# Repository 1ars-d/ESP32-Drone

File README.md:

# ESP32 Custom Drone

## 🚁 Overview

A compact, custom-built **5.5″ quadcopter drone** powered by an **ESP32 microcontroller**. This project includes both hardware design (3D-printed components, PCB layout) and firmware (Arduino-based) for flight control.

---

## 🔧 Firmware

The flight control software is written in **C++** using the **Arduino framework**. It runs a **250Hz control loop** to maintain drone stability using the following key features:

- **Sensor Fusion**: A **Kalman Filter** fuses gyroscope and accelerometer data to estimate orientation.
- **Control System**: Stabilization is achieved using a **cascaded PID control loop**.
- **Remote Input**: Directional control is handled via a **radio receiver**.
- **Live PID Tuning**: The drone can host a **local Wi-Fi web interface** for real-time PID tuning.
  > _The web-based tuning interface was adapted from [pratikPhadte/ESP32-Flight-controller-](https://github.com/pratikPhadte/ESP32-Flight-controller-)._

---

## 🛠️ Hardware Components

| Component             | Description                                                | Price   |
| --------------------- | ---------------------------------------------------------- | ------- |
| **Frame**             | FlyFishRC FIFTY5                                           | €50.00  |
| **Radio Receiver**    | Flysky FS-IA6B                                             | €20.00  |
| **Flight Controller** | ESP32-DevKitC, MP1584 (Buck Converter), MPU6050 (IMU), PCB | €20.00  |
| **Motors**            | 4x FlyfishRC Flash 2306 1750Kv                             | €60.00  |
| **ESC**               | 30.5mm 4-in-1 40A BLHeli32                                 | €50.00  |
| **Battery**           | 3S 1500mAh LiPo                                            | €20.00  |
| **Propellers**        | 4x 5.5″ Props                                              | €2.50   |
| **3D Printed Parts**  | Material cost for FC Case, RC Case, Feet                   | €2.00   |
| **Total**             |                                                            | €224,50 |

> Note: The listed prices are approximate and may vary depending on the retailer or manufacturer. In this build, we intentionally used some higher-quality (and more expensive) components to ensure that budget parts wouldn't become a limiting factor in performance. However, with careful sourcing and smart purchasing decisions, the overall cost of this drone can be significantly reduced.

---

## 🧠 Flight Controller

The flight controller (FC) is based on an **ESP32 DevKitC**, mounted on a custom PCB. It integrates:

- **MPU6050 IMU** for motion sensing
- **MP1584 buck converter** to step down 10V (from ESC) to 5V

Connections are made via **JST SH cables** to the ESC and radio receiver.

> ‼️ The VCC wire of the JST SH connector for the radio receiver is connected to the ESP32’s 3.3V output. However, the receiver used in this project (FS-IA6B) requires a minimum operating voltage of 4.0V. To address this, an additional VCC wire was manually soldered to the ESP32’s 5V pin to provide sufficient power. While some 5V receivers may appear to function at 3.3V in test setups, our testing showed that the receiver's output becomes unstable when the motors are running, likely due to temporary voltage drops. For reliable performance, ensure the receiver is properly powered with a stable 5V supply.

---

## 🧾 PCB Design

Designed using **KiCad** and manufactured by **JLCPCB**.

### 🔌 Schematic

### 🔄 Routing

### 3D Model

---

## 🖨️ 3D Printed Parts

All parts were designed in **Autodesk Fusion 360** and printed using **PLA**. **M2/M3 threaded heat inserts** are used to mount components to the carbon frame.

### 📦 Flight Controller Case

### 📡 Radio Receiver Case

### 🧩 Miscellaneous Parts

**Spacers**  

**Feet**  
Model from [Cults3D – FlyFishRC Volador Arm Protection](https://cults3d.com/de/modell-3d/spiel/flyfishrc-volador-5-6-full-arm-protection)  

---

## 👥 Contributors

- Tilman Kurmayer (https://github.com/tchello45)
- Melina Leitermann (https://github.com/me1ina1)

## 📚 References & Inspirations

This project was inspired and guided by the following open-source resources:

- [CarbonAeronautics/Manual-Quadcopter-Drone](https://github.com/CarbonAeronautics/Manual-Quadcopter-Drone)
- [pratikPhadte/ESP32-Flight-controller-](https://github.com/pratikPhadte/ESP32-Flight-controller-)

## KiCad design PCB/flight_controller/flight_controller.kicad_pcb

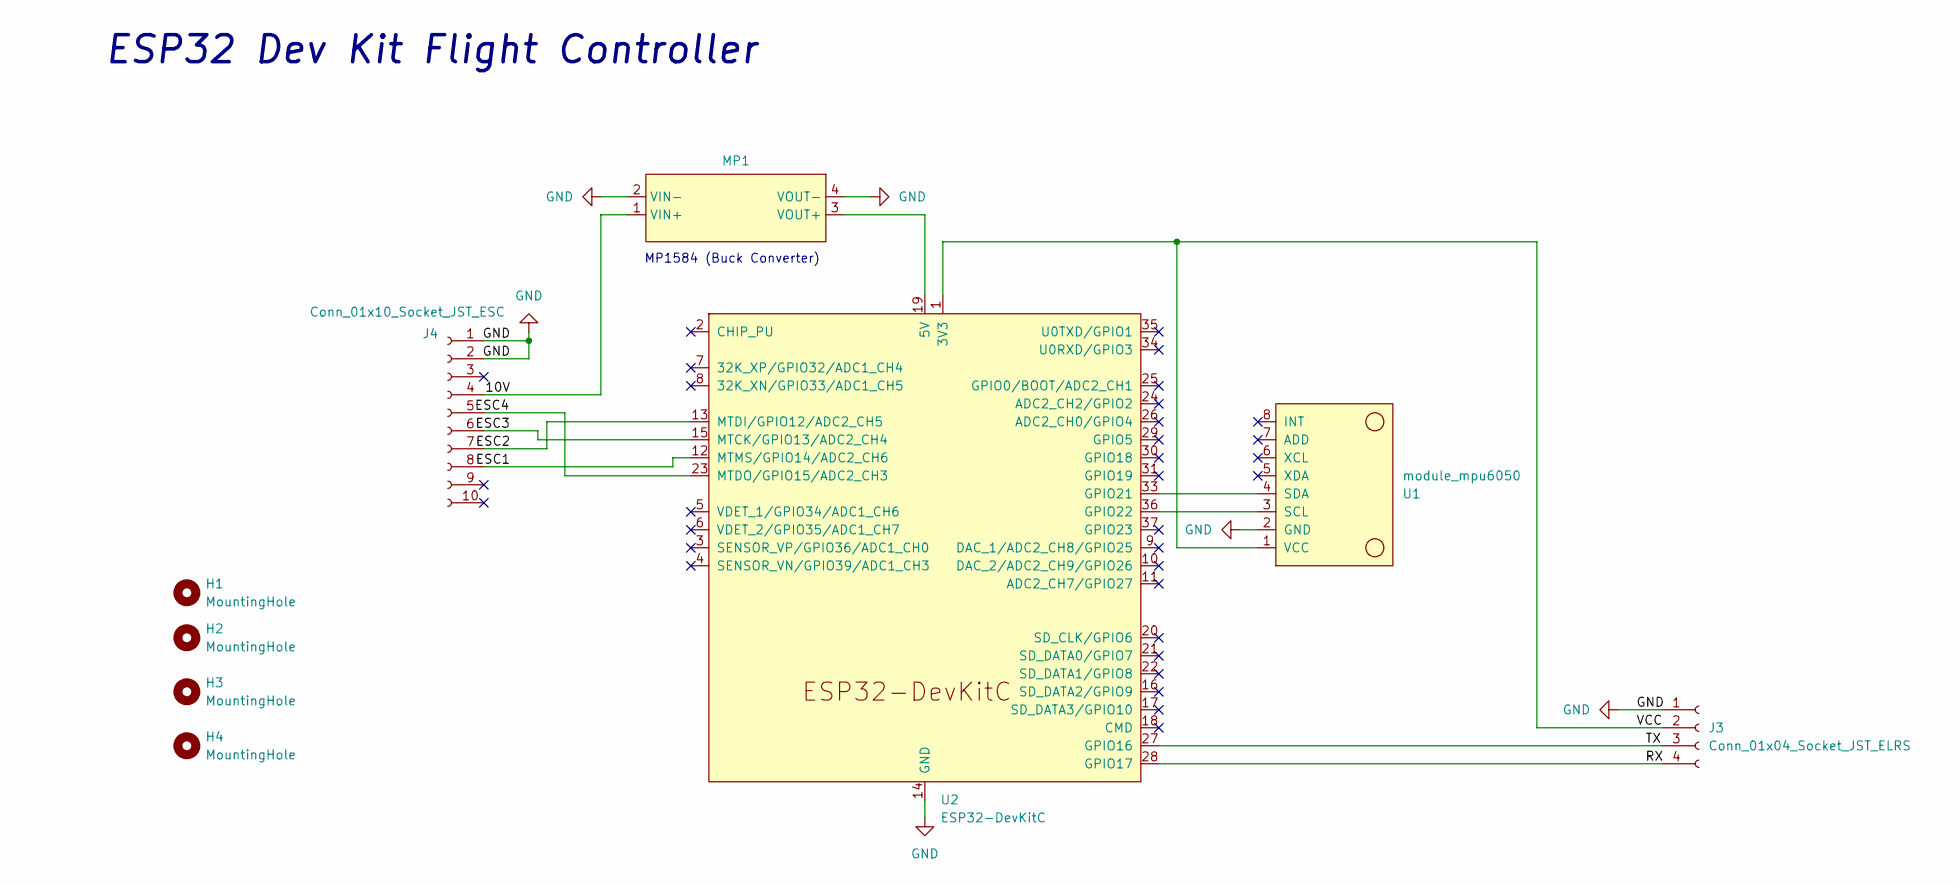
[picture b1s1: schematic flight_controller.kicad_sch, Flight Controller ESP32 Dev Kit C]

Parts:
H1, H2, H3, H4: MountingHole; MountingHole_2.2mm_M2
J3: Conn_01x04_Socket_JST_ELRS; JST_SH_SM04B-SRSS-TB_1x04-1MP_P1.00mm_Horizontal
J4: Conn_01x10_Socket_JST_ESC; JST_SH_SM10B-SRSS-TB_1x10-1MP_P1.00mm_Horizontal
MP1: SRT_MPT1584EN_Module
U1: module_mpu6050
U2: ESP32-DevKitC; ESP32 DevKitC Socket

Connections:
/10V: J4.4, MP1.1 (VIN+)
/ESC1: J4.8, U2.12 (MTMS/GPIO14/ADC2_CH6)
/ESC2: J4.7, U2.13 (MTDI/GPIO12/ADC2_CH5)
/ESC3: J4.6, U2.15 (MTCK/GPIO13/ADC2_CH4)
/ESC4: J4.5, U2.23 (MTDO/GPIO15/ADC2_CH3)
/RX: J3.4, U2.28 (GPIO17)
/TX: J3.3, U2.27 (GPIO16)
/VCC: J3.2, U1.1 (VCC), U2.1 (3V3)
GND: J3.1, J4.1, J4.2, MP1.2 (VIN-), MP1.4 (VOUT-), U1.2 (GND), U2.14 (GND), U2.32 (GND), U2.38 (GND)
unnamed: MP1.3 (VOUT+), U2.19 (5V)
unnamed: U1.3 (SCL), U2.36 (GPIO22)
unnamed: U1.4 (SDA), U2.33 (GPIO21)

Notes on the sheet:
MP1584 (Buck Converter)
ESP32 Dev Kit Flight Controller

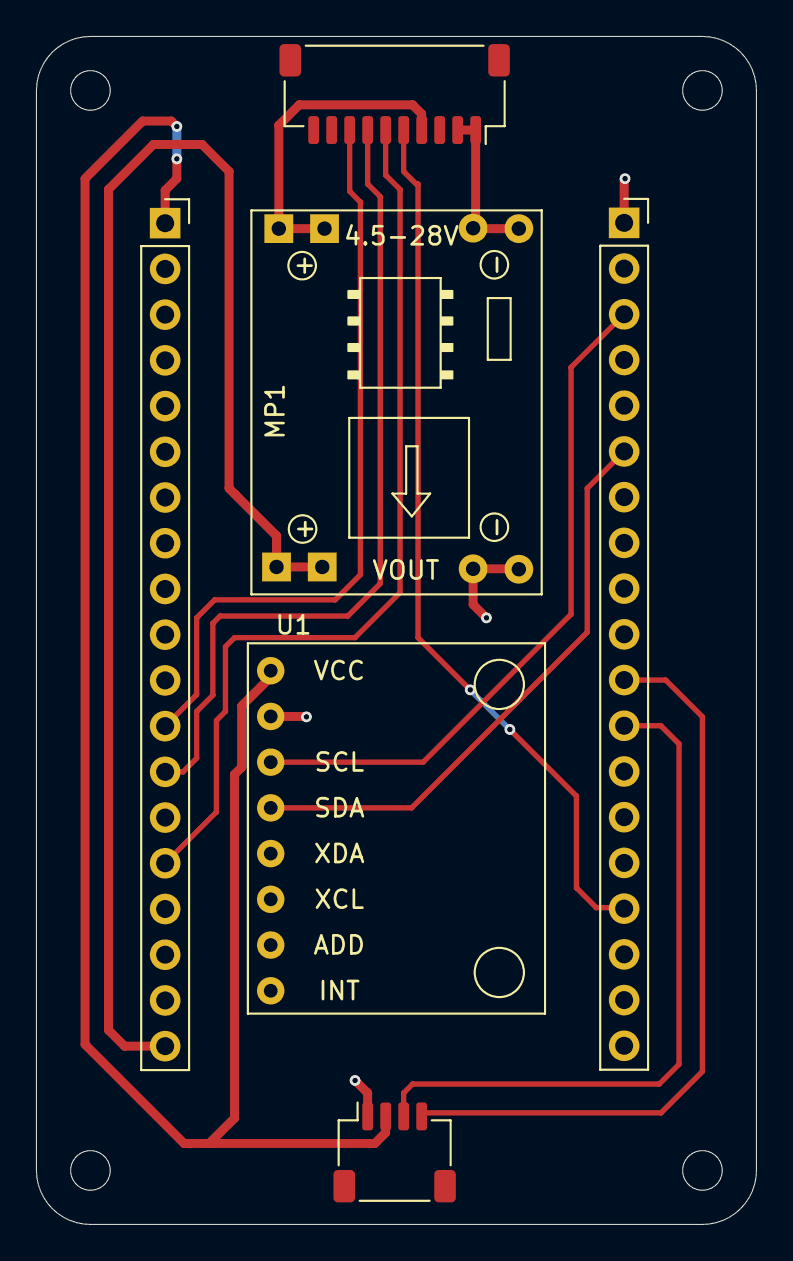
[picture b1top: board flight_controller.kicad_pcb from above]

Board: 2 copper layers, 40.0 x 66.0 mm, 9 parts (0 on the bottom side), 12 nets.

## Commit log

2025-04-18 pcb create symbols and footprints
2025-05-18 start README.md
2025-05-18 PCB updates
2025-05-18 downscaled images
